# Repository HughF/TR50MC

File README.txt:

TR50MC repository contents:

There are two KiCad projects, one for the internal PCB (pulseremote), one for the front panel (richardpanel).

I suggest the user downloads all these files, extracts them to a single directory then uses the KiCad PCB viewer to open the relevant files from the correct directory.

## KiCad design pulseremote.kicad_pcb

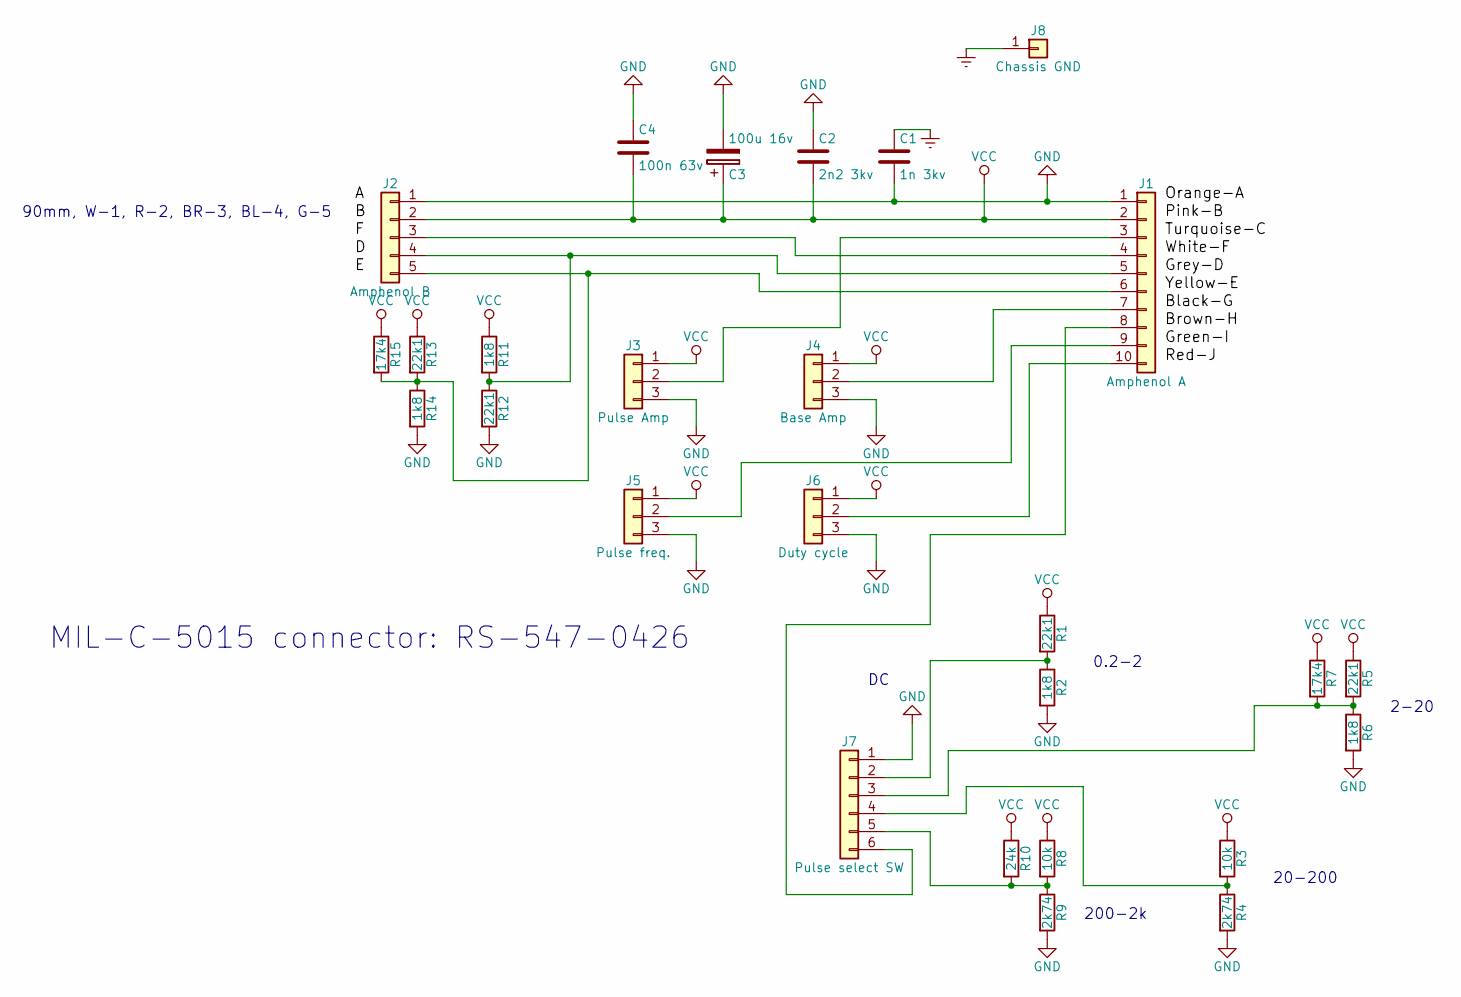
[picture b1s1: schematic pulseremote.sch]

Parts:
C1: 1n 3kv; C_Disc_D10.0mm_W2.5mm_P5.00mm
C2: 2n2 3kv; C_Disc_D10.0mm_W2.5mm_P5.00mm
C3: 100u 16v; CP_Tantalum_Case-A_EIA-3216-18_Hand
C4: 100n 63v; C_1206_HandSoldering
J1: Amphenol A; JST_XH_B10B-XH-A_1x10_P2.50mm_Vertical
J2: Amphenol B; JST_XH_B05B-XH-A_1x05_P2.50mm_Vertical
J3: Pulse Amp; JST_XH_B03B-XH-A_1x03_P2.50mm_Vertical
J4: Base Amp; JST_XH_B03B-XH-A_1x03_P2.50mm_Vertical
J5: Pulse freq.; JST_XH_B03B-XH-A_1x03_P2.50mm_Vertical
J6: Duty cycle; JST_XH_B03B-XH-A_1x03_P2.50mm_Vertical
J7: Pulse select SW; JST_XH_B06B-XH-A_1x06_P2.50mm_Vertical
J8: Chassis GND; SolderWirePad_single_2-5mmDrill
R1, R5, R12, R13: 22k1; R_1206_HandSoldering
R2, R6, R11, R14: 1k8; R_1206_HandSoldering
R3, R8: 10k; R_1206_HandSoldering
R4, R9: 2k74; R_1206_HandSoldering
R7, R15: 17k4; R_1206_HandSoldering
R10: 24k; R_1206_HandSoldering

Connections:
Earth: C1.1, J8.1
GND: C1.2, C2.1, C3.2, C4.1, J1.1, J2.1, J3.3, J4.3, J5.3, J6.3, J7.1, R2.2, R4.2, R6.2, R9.2, R12.2, R14.2
unnamed: J1.3, J3.2
unnamed: J1.4, J2.3
unnamed: J1.5, J2.4, R11.2, R12.1
unnamed: J1.6, J2.5, R13.2, R14.1, R15.2
unnamed: J1.7, J4.2
unnamed: J1.8, J7.6
unnamed: J1.9, J5.2
unnamed: J1.10, J6.2
unnamed: J7.2, R1.2, R2.1
unnamed: J7.3, R5.2, R6.1, R7.2
unnamed: J7.4, R3.2, R4.1
unnamed: J7.5, R8.2, R9.1, R10.2
VCC: C2.2, C3.1, C4.2, J1.2, J2.2, J3.1, J4.1, J5.1, J6.1, R1.1, R3.1, R5.1, R7.1, R8.1, R10.1, R11.1, R13.1, R15.1

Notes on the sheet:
MIL-C-5015 connector: RS-547-0426
90mm, W-1, R-2, BR-3, BL-4, G-5
0.2-2
2-20
20-200
200-2k

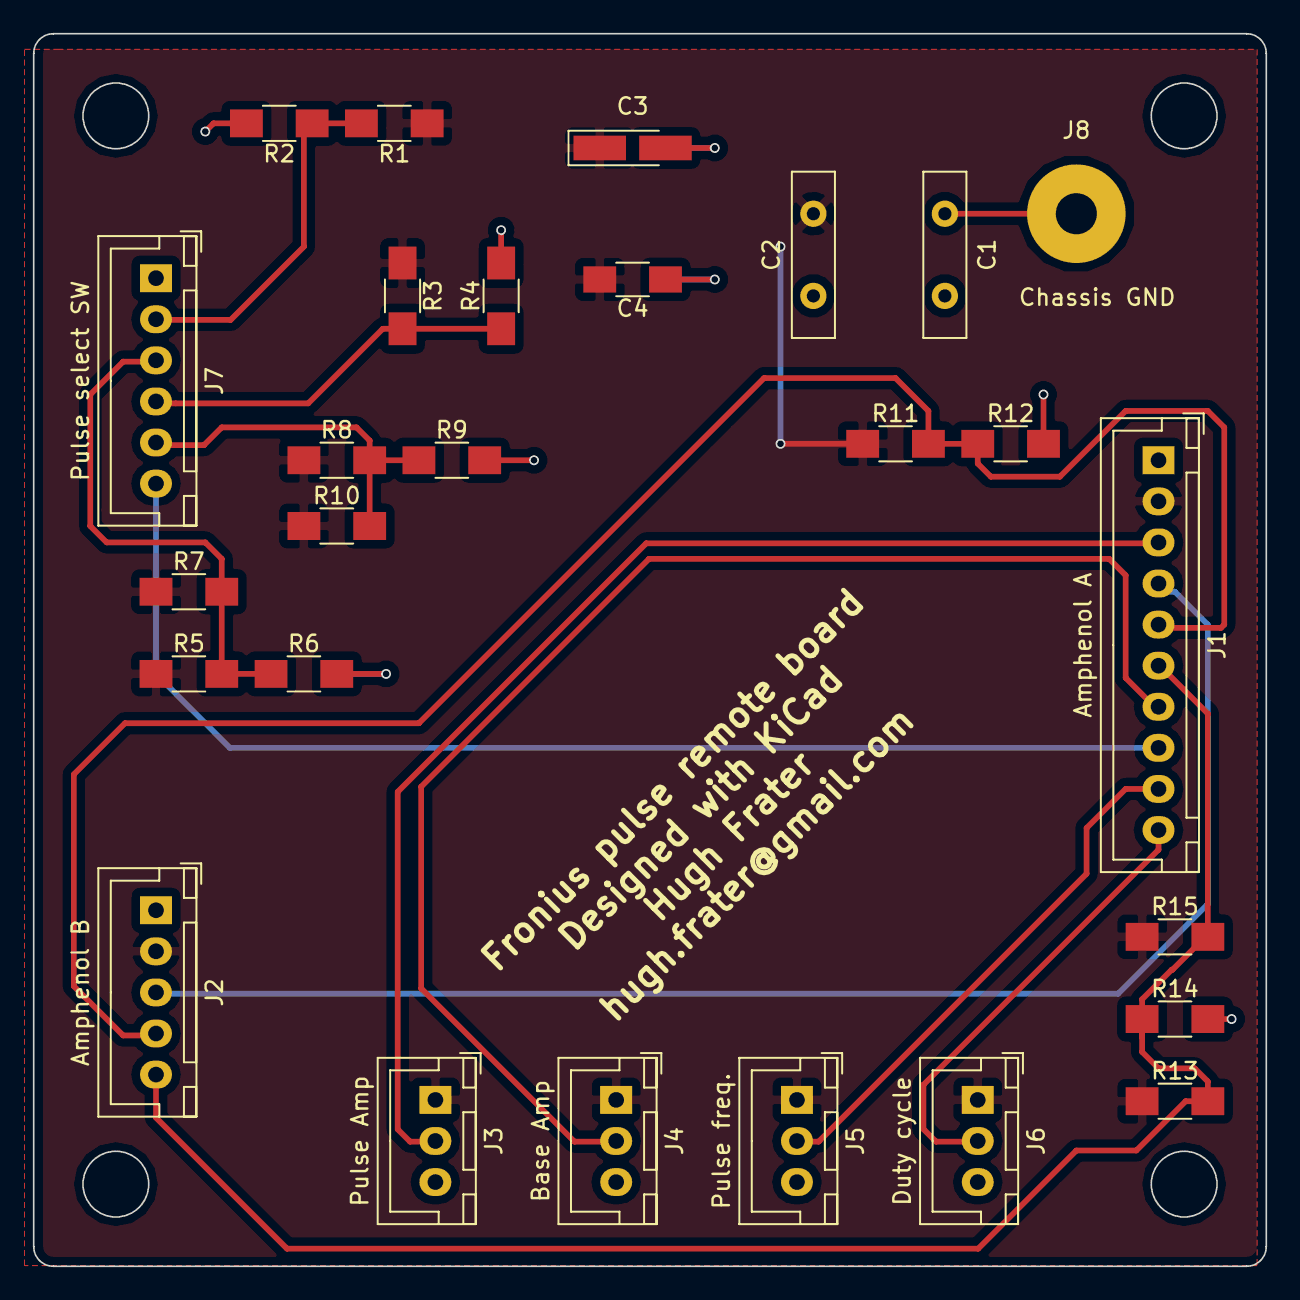
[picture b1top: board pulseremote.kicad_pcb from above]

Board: 2 copper layers, 75.0 x 75.0 mm, 27 parts (0 on the bottom side), 15 nets.
